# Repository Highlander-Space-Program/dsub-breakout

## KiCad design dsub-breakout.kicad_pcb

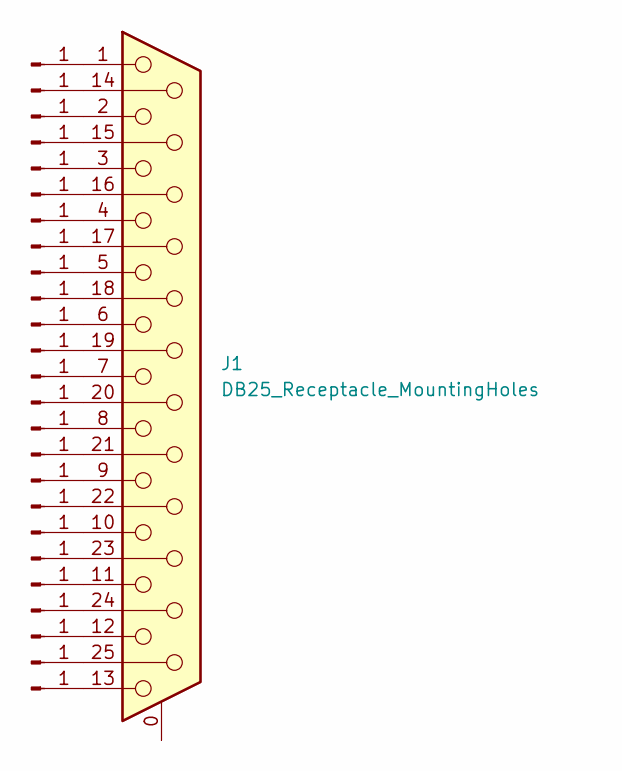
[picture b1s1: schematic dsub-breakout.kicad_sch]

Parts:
J1: DB25_Receptacle_MountingHoles; DSUB-25_Female_Vertical_P2.77x2.84mm_MountingHoles
J2, J3, J4, J5, J6, J7, J8, J9, J10, J11, J12, J13, J14, J15, J16, J17, J18, J19, J20, J21, J22, J23, J24, J25, J26: Conn_01x01_Pin; SolderWire-0.25sqmm_1x01_D0.65mm_OD2mm_Relief

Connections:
unnamed: J1.14, J3.1
unnamed: J1.15, J5.1
unnamed: J1.16, J7.1
unnamed: J1.17, J9.1
unnamed: J1.18, J11.1
unnamed: J1.19, J13.1
unnamed: J1.20, J15.1
unnamed: J1.21, J17.1
unnamed: J1.22, J19.1
unnamed: J1.23, J21.1
unnamed: J1.24, J23.1
unnamed: J1.25, J25.1
unnamed: J1.1, J2.1
unnamed: J1.2, J4.1
unnamed: J1.3, J6.1
unnamed: J1.4, J8.1
unnamed: J1.5, J10.1
unnamed: J1.6, J12.1
unnamed: J1.7, J14.1
unnamed: J1.8, J16.1
unnamed: J1.9, J18.1
unnamed: J1.10, J20.1
unnamed: J1.11, J22.1
unnamed: J1.12, J24.1
unnamed: J1.13, J26.1

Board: 2 copper layers, 26 parts (0 on the bottom side), 25 nets, no tracks yet.

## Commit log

2024-01-24 Initial board schematic & layout
